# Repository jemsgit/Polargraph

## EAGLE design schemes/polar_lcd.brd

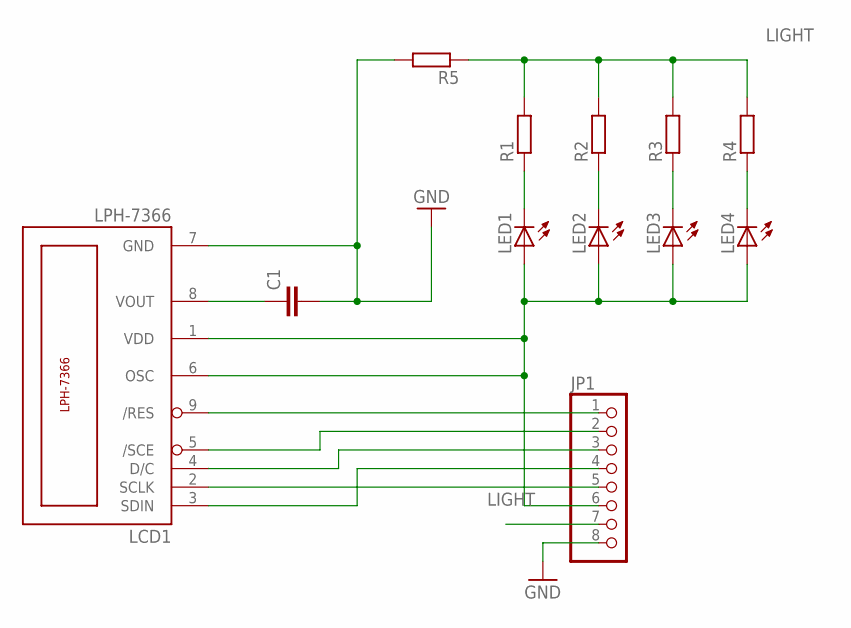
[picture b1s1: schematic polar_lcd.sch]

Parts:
C1: C-EUC0805; C0805
JP1: PINHD-1X8; 1X08
LCD1: LPH-7366
LED1, LED2, LED3, LED4: LEDSMT1206; 1206
R1, R2, R3, R4, R5: R-EU_R0805; R0805

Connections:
GND: C1.2, JP1.8, LCD1.7 (GND), R5.2
LIGHT: JP1.7, R1.2, R2.2, R3.2, R4.2, R5.1
unnamed: JP1.1, LCD1.9 (/RES)
unnamed: C1.1, LCD1.8 (VOUT)
unnamed: JP1.6, LCD1.1 (VDD), LCD1.6 (OSC), LED1.A, LED2.A, LED3.A, LED4.A
unnamed: LED1.C, R1.1
unnamed: LED2.C, R2.1
unnamed: LED3.C, R3.1
unnamed: LED4.C, R4.1
unnamed: JP1.5, LCD1.2 (SCLK)
unnamed: JP1.4, LCD1.3 (SDIN)
unnamed: JP1.3, LCD1.4 (D/C)
unnamed: JP1.2, LCD1.5 (/SCE)

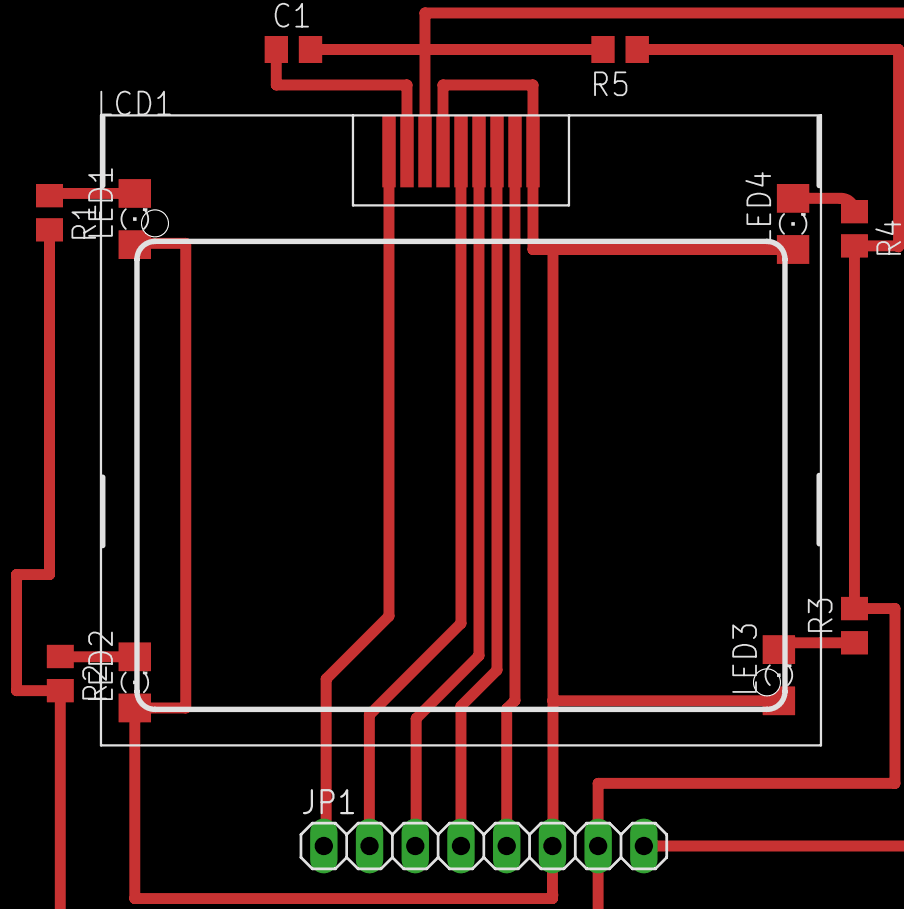
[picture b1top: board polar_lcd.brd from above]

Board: 2 copper layers, 12 parts (0 on the bottom side), 13 nets.

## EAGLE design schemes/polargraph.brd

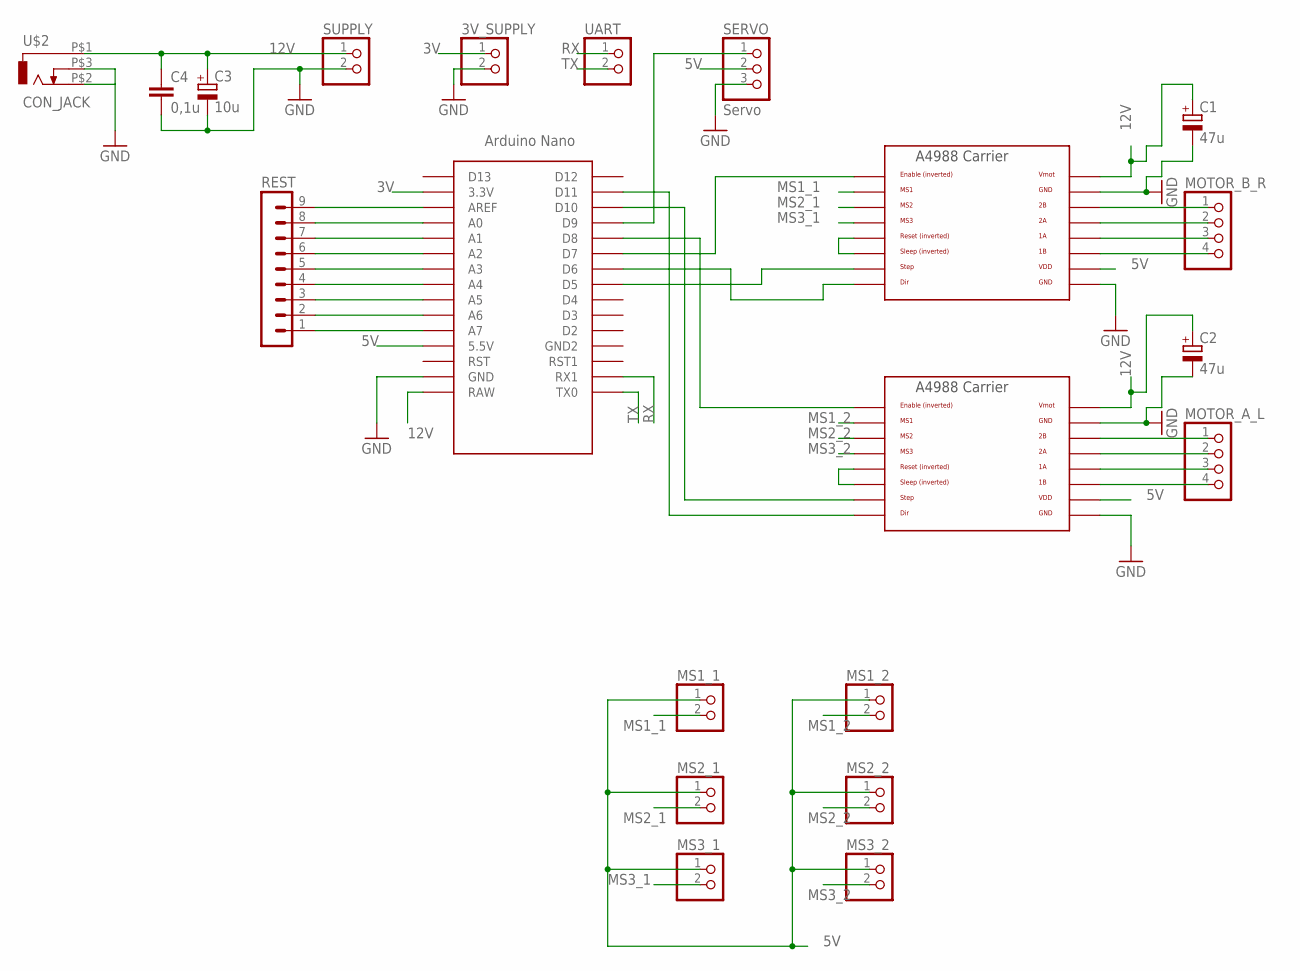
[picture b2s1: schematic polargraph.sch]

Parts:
3V_SUPPLY: PINHD-1X2; 1X02
C1, C2: 47u; E3,5-10
C3: 10u; E3,5-10
C4: 0,1u; C0805
DRIVER_LEFT: A4988BREAKOUT
DRIVER_R: A4988BREAKOUT
MOTOR_A_L: PINHD-1X4; 1X04
MOTOR_B_R: PINHD-1X4; 1X04
MS1_1, MS1_2, MS2_1, MS2_2, MS3_1, MS3_2: PINHD-1X2; 1X02
REST: MA09-1
SERVO: Servo; 1X03
SUPPLY: PINHD-1X2; 1X02
U$1: NANO
U$2: CON_JACK
UART: PINHD-1X2; 1X02

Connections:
3V: 3V_SUPPLY.1, U$1.3.3V
5V: DRIVER_LEFT.VDD, DRIVER_R.VDD, MS1_1.1, MS1_2.1, MS2_1.1, MS2_2.1, MS3_1.1, MS3_2.1, SERVO.2, U$1.5V (5.5V)
12V: C1.+, C2.+, C3.+, C4.1, DRIVER_LEFT.VMOT, DRIVER_R.VMOT, SUPPLY.1, U$1.RAW, U$2.P$1 (V1)
GND: 3V_SUPPLY.2, C1.-, C2.-, C3.-, C4.2, DRIVER_LEFT.GND, DRIVER_LEFT.GND@0 (GND), DRIVER_R.GND, DRIVER_R.GND@0 (GND), SERVO.3, SUPPLY.2, U$1.GND, U$2.P$2 (G3), U$2.P$3 (G2)
MS1_1: DRIVER_R.MS1, MS1_1.2
MS1_2: DRIVER_LEFT.MS1, MS1_2.2
MS2_1: DRIVER_R.MS2, MS2_1.2
MS2_2: DRIVER_LEFT.MS2, MS2_2.2
MS3_1: DRIVER_R.MS3, MS3_1.2
MS3_2: DRIVER_LEFT.MS3, MS3_2.2
unnamed: DRIVER_R.RST, DRIVER_R.SLP (SLEEP)
unnamed: DRIVER_LEFT.RST, DRIVER_LEFT.SLP (SLEEP)
unnamed: DRIVER_LEFT.2B, MOTOR_A_L.1
unnamed: DRIVER_LEFT.2A, MOTOR_A_L.2
unnamed: DRIVER_LEFT.1A, MOTOR_A_L.3
unnamed: DRIVER_LEFT.1B, MOTOR_A_L.4
unnamed: DRIVER_R.2B, MOTOR_B_R.1
unnamed: DRIVER_R.2A, MOTOR_B_R.2
unnamed: DRIVER_R.1A, MOTOR_B_R.3
unnamed: DRIVER_R.1B, MOTOR_B_R.4
unnamed: DRIVER_R.EN, U$1.D7
unnamed: DRIVER_R.STEP, U$1.D5
unnamed: DRIVER_R.DIR, U$1.D6
unnamed: DRIVER_LEFT.EN, U$1.D8
unnamed: DRIVER_LEFT.STEP, U$1.D10
unnamed: DRIVER_LEFT.DIR, U$1.D11
unnamed: SERVO.1, U$1.D9
unnamed: REST.9, U$1.AREF
unnamed: REST.8, U$1.A0
unnamed: REST.7, U$1.A1
unnamed: REST.6, U$1.A2
unnamed: REST.5, U$1.A3
unnamed: REST.4, U$1.A4
unnamed: REST.3, U$1.A5
unnamed: REST.2, U$1.A6
unnamed: REST.1, U$1.A7
RX: U$1.RX1, UART.1
TX: U$1.TX0, UART.2

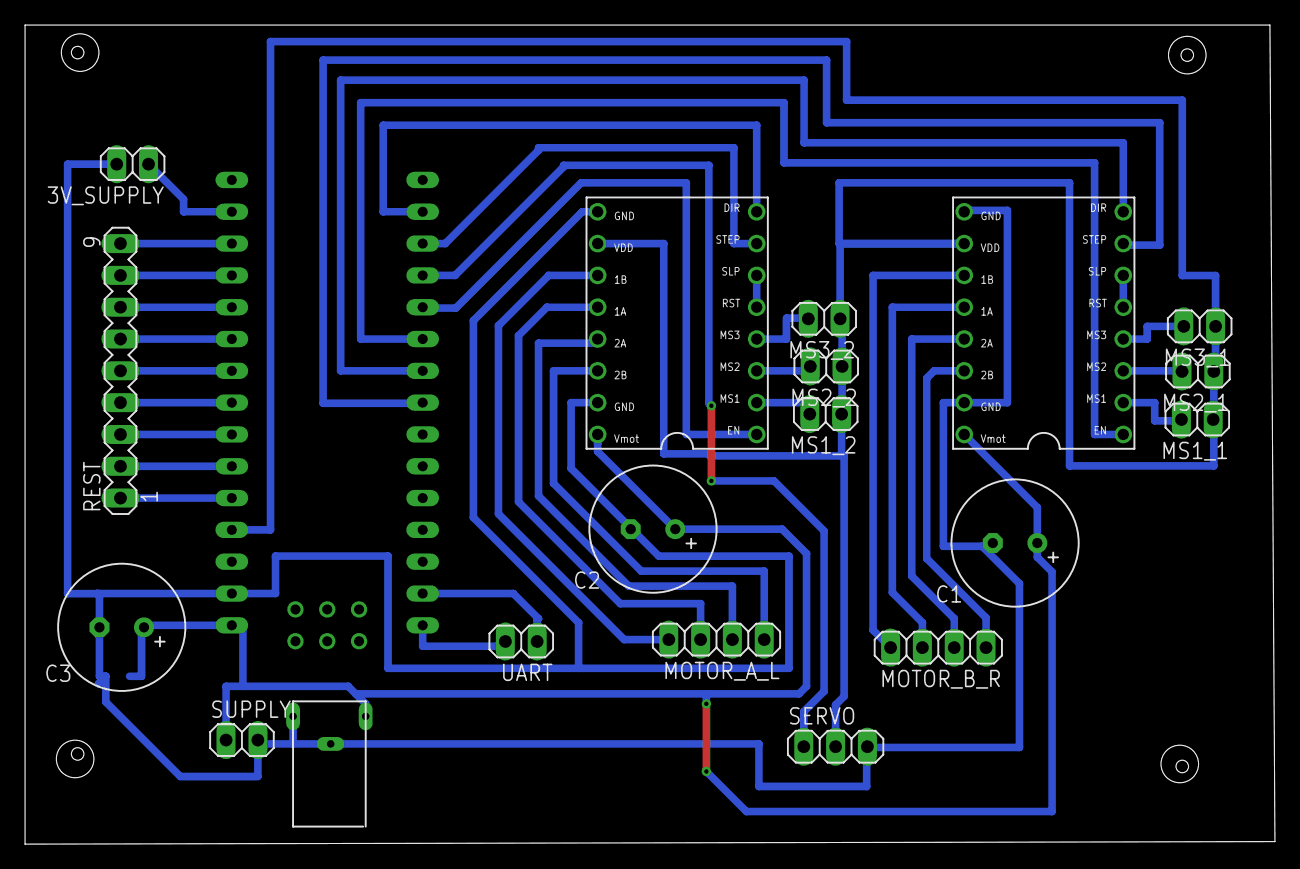
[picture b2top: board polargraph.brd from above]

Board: 2 copper layers, 99.8 x 65.4 mm, 21 parts (1 on the bottom side), 38 nets.

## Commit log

2019-05-12 polargraph stuff
